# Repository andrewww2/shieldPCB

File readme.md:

Arduino shield for CaBot (2nd try)
=============================

Using this for an Arduino MEGA shield template: https://github.com/zortness/rocket-mega-shield

The motor driver is copied from the Solarbotics L298 driver: https://solarbotics.com/product/k_cmd/

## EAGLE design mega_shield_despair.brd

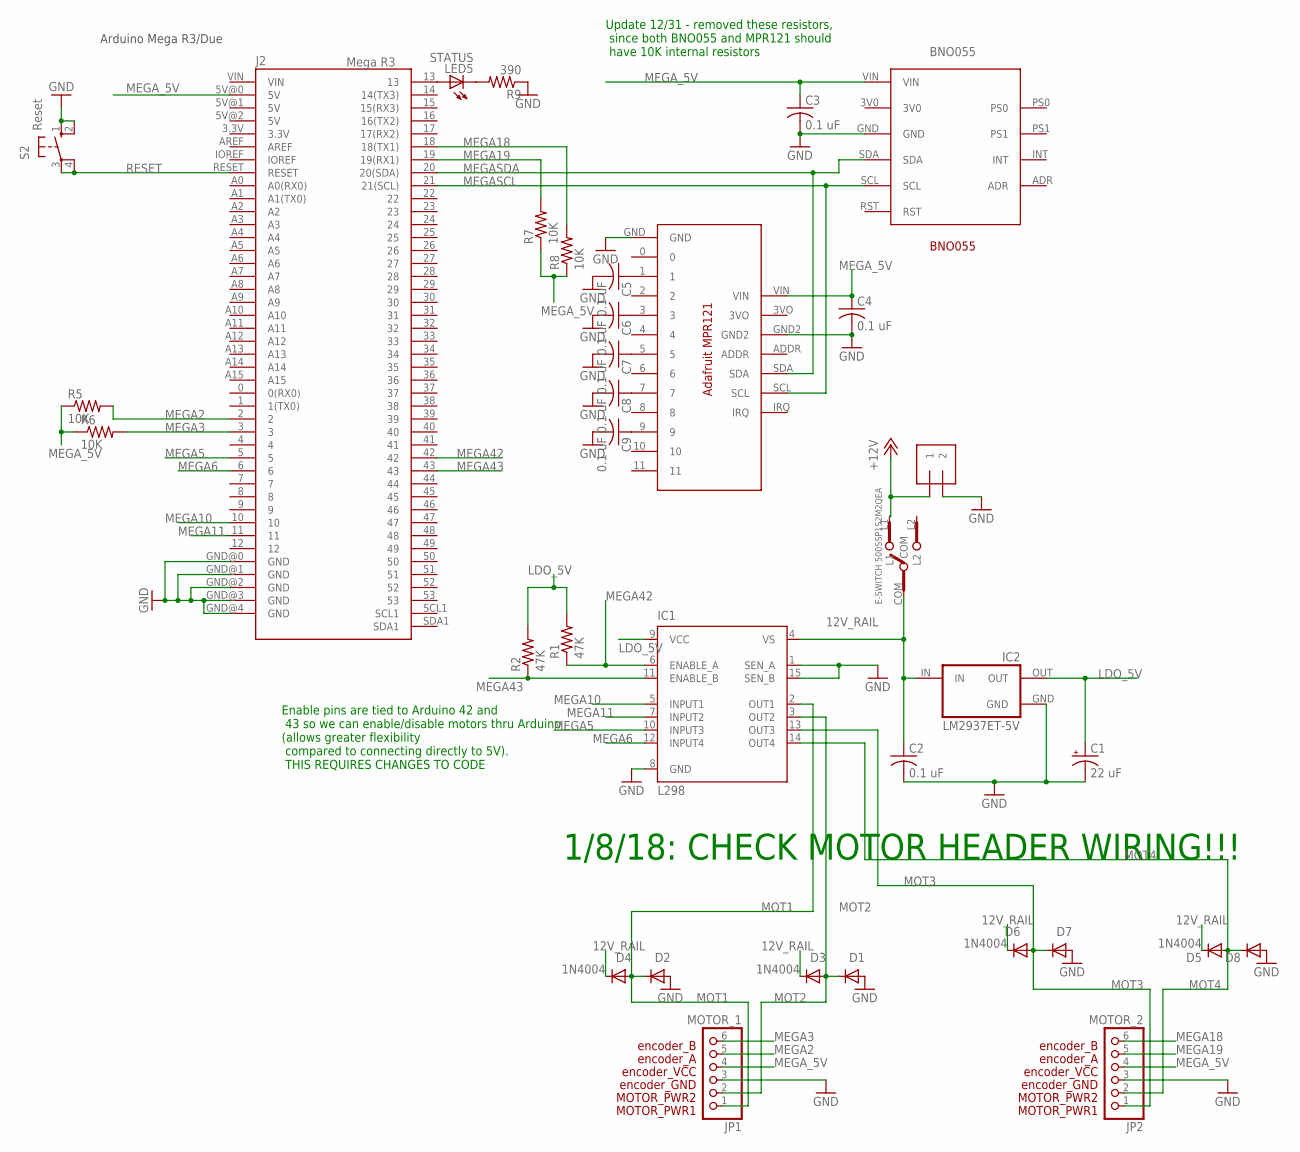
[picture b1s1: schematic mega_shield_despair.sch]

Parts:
12V_IN: 1X2-3.5MM
BNO055: BNO055
C1: 22 uF; B45181A
C2, C3, C4, C5, C6, C7, C8, C9: 0.1 uF; C025-050X050
D1, D2, D3, D4, D5, D6, D7, D8: 1N4004; DO41-10
IC1: L298; MULTIWATT-15
IC2: LM2937ET-5V; TO220(V)
J2: Mega R3; ARDUINO_MEGA
JP1: MOTOR_1; 1X06
JP2: MOTOR_2; 1X06
LED5: STATUS; LED3MM
MPR121: ADA_MPR121
R1, R2: 47K; 0207/10
R5, R6, R7, R8: 10K; 0207/10
R9: 390; 0207/10
S2: Reset; B3F-10XX
SLIDE_SW: E-SWITCH_500SSP1S2M2QEA

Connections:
12V_RAIL: C2.1, D3.C, D4.C, D5.C, D6.C, IC1.4 (VS), IC2.IN, SLIDE_SW.COM
+12V: 12V_IN.1, SLIDE_SW.L1
GND: 12V_IN.2, BNO055.GND, C1.-, C2.2, C3.2, C4.2, C5.2, C6.2, C7.2, C8.2, C9.2, D1.A, D2.A, D7.A, D8.A, IC1.1 (SEN_A), IC1.8 (GND), IC1.15 (SEN_B), IC2.GND, J2.GND@0 (GND), J2.GND@1 (GND), J2.GND@2 (GND), J2.GND@3 (GND), J2.GND@4 (GND), JP1.3, JP2.3, MPR121.GND, MPR121.GND2, R9.1, S2.1 (S), S2.2 (S1)
LDO_5V: C1.+, IC1.9 (VCC), IC2.OUT, R1.2, R2.2
MEGA2: J2.2, JP1.5, R5.2
MEGA3: J2.3, JP1.6, R6.2
MEGA5: IC1.10 (INPUT3), J2.5
MEGA6: IC1.12 (INPUT4), J2.6
MEGA10: IC1.5 (INPUT1), J2.10
MEGA11: IC1.7 (INPUT2), J2.11
MEGA18: J2.18 (18(TX1)), JP2.6, R8.2
MEGA19: J2.19 (19(RX1)), JP2.5, R7.2
MEGA42: IC1.6 (ENABLE_A), J2.42, R1.1
MEGA43: IC1.11 (ENABLE_B), J2.43, R2.1
MEGASCL: BNO055.SCL, J2.21 (21(SCL)), MPR121.SCL
MEGASDA: BNO055.SDA, J2.20 (20(SDA)), MPR121.SDA
MEGA_5V: BNO055.VIN, C3.1, C4.1, J2.5V@0 (5V), JP1.4, JP2.4, MPR121.VIN, R5.1, R6.1, R7.1, R8.1
MOT1: D2.C, D4.A, IC1.2 (OUT1), JP1.1
MOT2: D1.C, D3.A, IC1.3 (OUT2), JP1.2
MOT3: D6.A, D7.C, IC1.13 (OUT3), JP2.1
MOT4: D5.A, D8.C, IC1.14 (OUT4), JP2.2
unnamed: C5.1, MPR121.1
unnamed: C6.1, MPR121.3
unnamed: J2.13, LED5.A
unnamed: LED5.K (C), R9.2
unnamed: C7.1, MPR121.5
unnamed: C8.1, MPR121.7
unnamed: C9.1, MPR121.9
RESET: J2.RESET, S2.3, S2.4 (P1)

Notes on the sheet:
Arduino Mega R3/Due
Update 12/31 - removed these resistors, since both BNO055 and MPR121 should have 10K internal resistors
Enable pins are tied to Arduino 42 and 43 so we can enable/disable motors thru Arduino (allows greater flexibility compared to connecting directly to 5V). THIS REQUIRES CHANGES TO CODE
1/8/18: CHECK MOTOR HEADER WIRING!!!

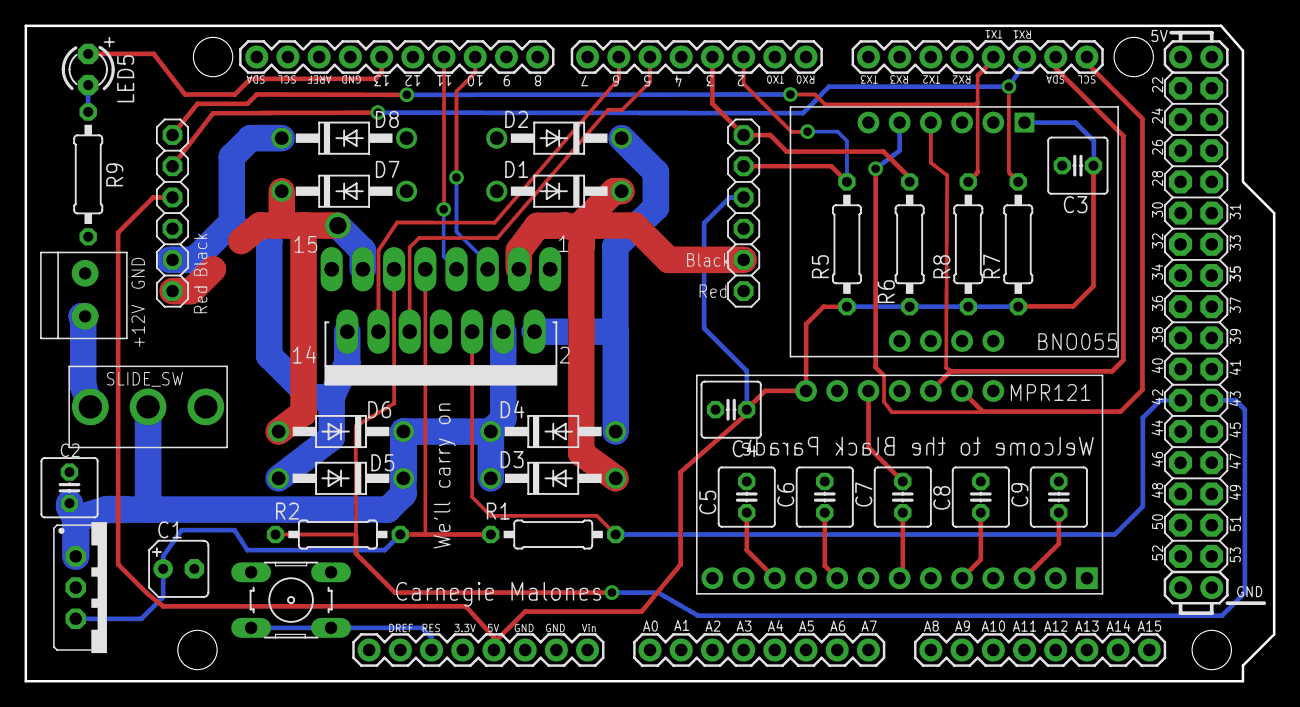
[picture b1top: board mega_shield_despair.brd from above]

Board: 2 copper layers, 101.6 x 53.3 mm, 35 parts (0 on the bottom side), 29 nets.

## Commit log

2018-01-07 Init commit
2018-01-07 removed unrelated files
2018-01-07 remove DS store
2018-01-07 Updated readme, added ESD pdf
2018-01-07 Minor changs to component placement
2018-01-08 Added 6 pin motor headers
2018-01-13 Add updated component list
2018-01-17 Added restricts to ground plane in brd file
2018-01-17 Added switch to library, shifted components around on brd
2018-01-19 added excel component list, changed resistor values
2018-01-24 changes to silkscreen
2018-01-25 shifted some components around, edited silkscreen
2018-01-26 final gerber files
2018-02-21 add despair version
